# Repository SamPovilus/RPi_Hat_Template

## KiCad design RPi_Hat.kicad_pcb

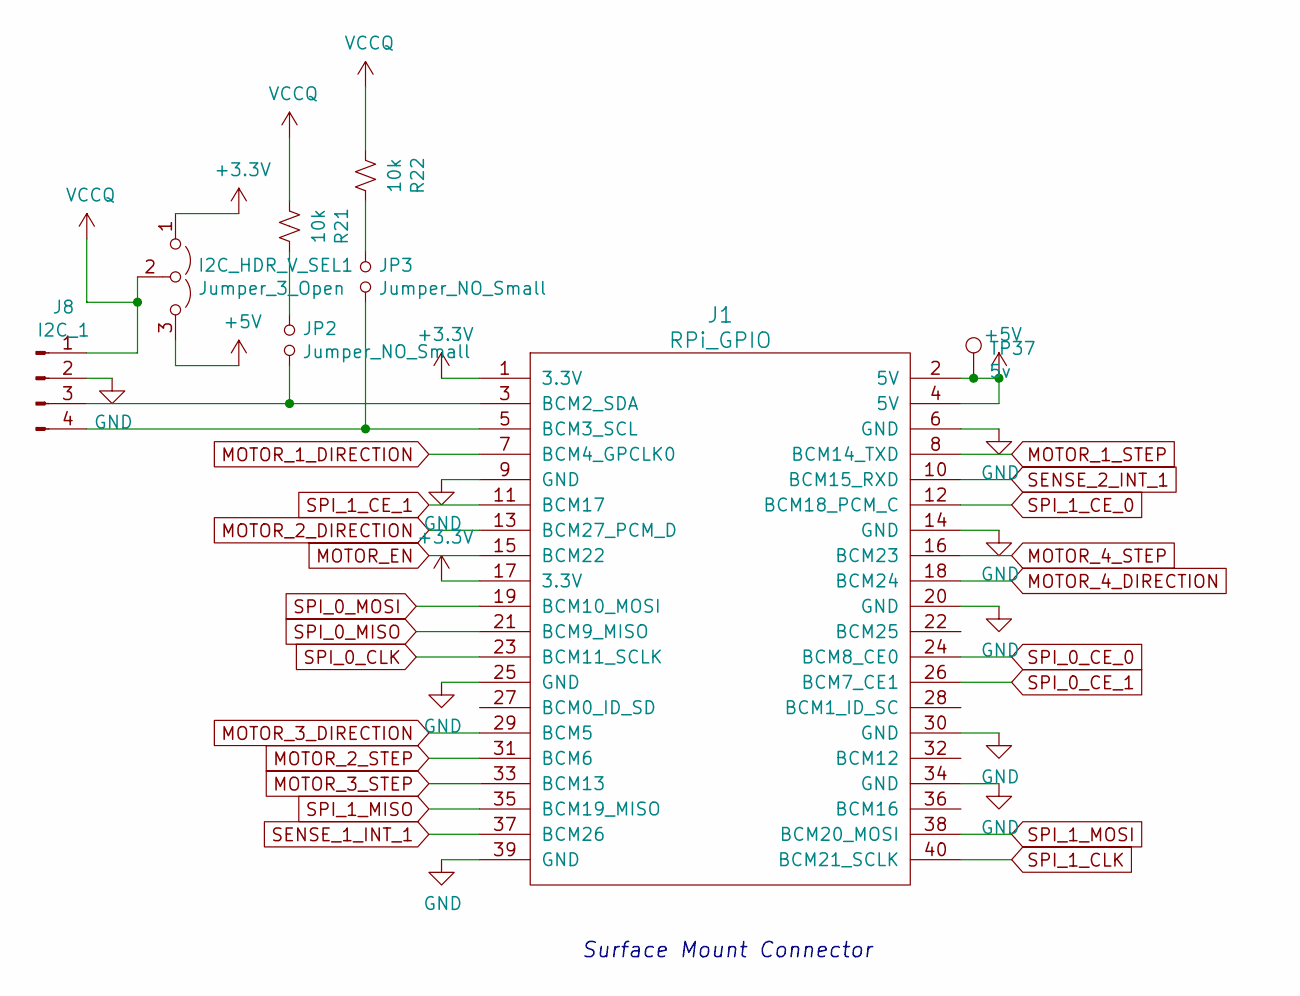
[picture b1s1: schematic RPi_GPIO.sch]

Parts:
I2C_HDR_V_SEL1: Jumper_3_Open; SAMTEC-TSM-103-01-X-SH
J1: RPi_GPIO; Samtec_HLE-120-02-XXX-DV-BE-XX-XX
J8: I2C_1; SAMTEC-TSM-102-01-X-DH
JP2, JP3: Jumper_NO_Small; SolderJumper-2_P1.3mm_Open_TrianglePad1.0x1.5mm
R21, R22: 10k; C_0805_2012Metric_Pad1.18x1.45mm_HandSolder
TP37: 5v; TestPoint_Keystone_5015_Micro-Minature

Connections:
+3V3: I2C_HDR_V_SEL1.1 (A), J1.1 (3.3V), J1.17 (3.3V); also elsewhere on the board
+5V: I2C_HDR_V_SEL1.3 (B), J1.2 (5V), J1.4 (5V), TP37.1; also elsewhere on the board
GND: J1.6 (GND), J1.9 (GND), J1.14 (GND), J1.20 (GND), J1.25 (GND), J1.30 (GND), J1.34 (GND), J1.39 (GND), J8.2; also elsewhere on the board
MOTOR_1_DIRECTION: J1.7 (BCM4_GPCLK0); also elsewhere on the board
MOTOR_1_STEP: J1.8 (BCM14_TXD); also elsewhere on the board
MOTOR_2_DIRECTION: J1.13 (BCM27_PCM_D); also elsewhere on the board
MOTOR_2_STEP: J1.31 (BCM6); also elsewhere on the board
MOTOR_3_DIRECTION: J1.29 (BCM5); also elsewhere on the board
MOTOR_3_STEP: J1.33 (BCM13); also elsewhere on the board
MOTOR_4_DIRECTION: J1.18 (BCM24); also elsewhere on the board
MOTOR_4_STEP: J1.16 (BCM23); also elsewhere on the board
MOTOR_EN: J1.15 (BCM22); also elsewhere on the board
unnamed 34: J1.3 (BCM2_SDA), J8.3, JP2.2; also elsewhere on the board
unnamed 35: J1.5 (BCM3_SCL), J8.4, JP3.2; also elsewhere on the board
unnamed 36: J1.22 (BCM25); also elsewhere on the board
unnamed 37: J1.27 (BCM0_ID_SD); also elsewhere on the board
unnamed 38: J1.28 (BCM1_ID_SC); also elsewhere on the board
unnamed 39: J1.32 (BCM12); also elsewhere on the board
unnamed 40: J1.36 (BCM16); also elsewhere on the board
unnamed: JP2.1, R21.1
unnamed: JP3.1, R22.1
SENSE_1_INT_1: J1.37 (BCM26); also elsewhere on the board
SENSE_2_INT_1: J1.10 (BCM15_RXD); also elsewhere on the board
SPI_0_CE_0: J1.24 (BCM8_CE0); also elsewhere on the board
SPI_0_CE_1: J1.26 (BCM7_CE1); also elsewhere on the board
SPI_0_CLK: J1.23 (BCM11_SCLK); also elsewhere on the board
SPI_0_MISO: J1.21 (BCM9_MISO); also elsewhere on the board
SPI_0_MOSI: J1.19 (BCM10_MOSI); also elsewhere on the board
SPI_1_CE_0: J1.12 (BCM18_PCM_C); also elsewhere on the board
SPI_1_CE_1: J1.11 (BCM17); also elsewhere on the board
SPI_1_CLK: J1.40 (BCM21_SCLK); also elsewhere on the board
SPI_1_MISO: J1.35 (BCM19_MISO); also elsewhere on the board
SPI_1_MOSI: J1.38 (BCM20_MOSI); also elsewhere on the board
VCCQ: I2C_HDR_V_SEL1.2 (C), J8.1, R21.2, R22.2

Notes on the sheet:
Surface Mount Connector

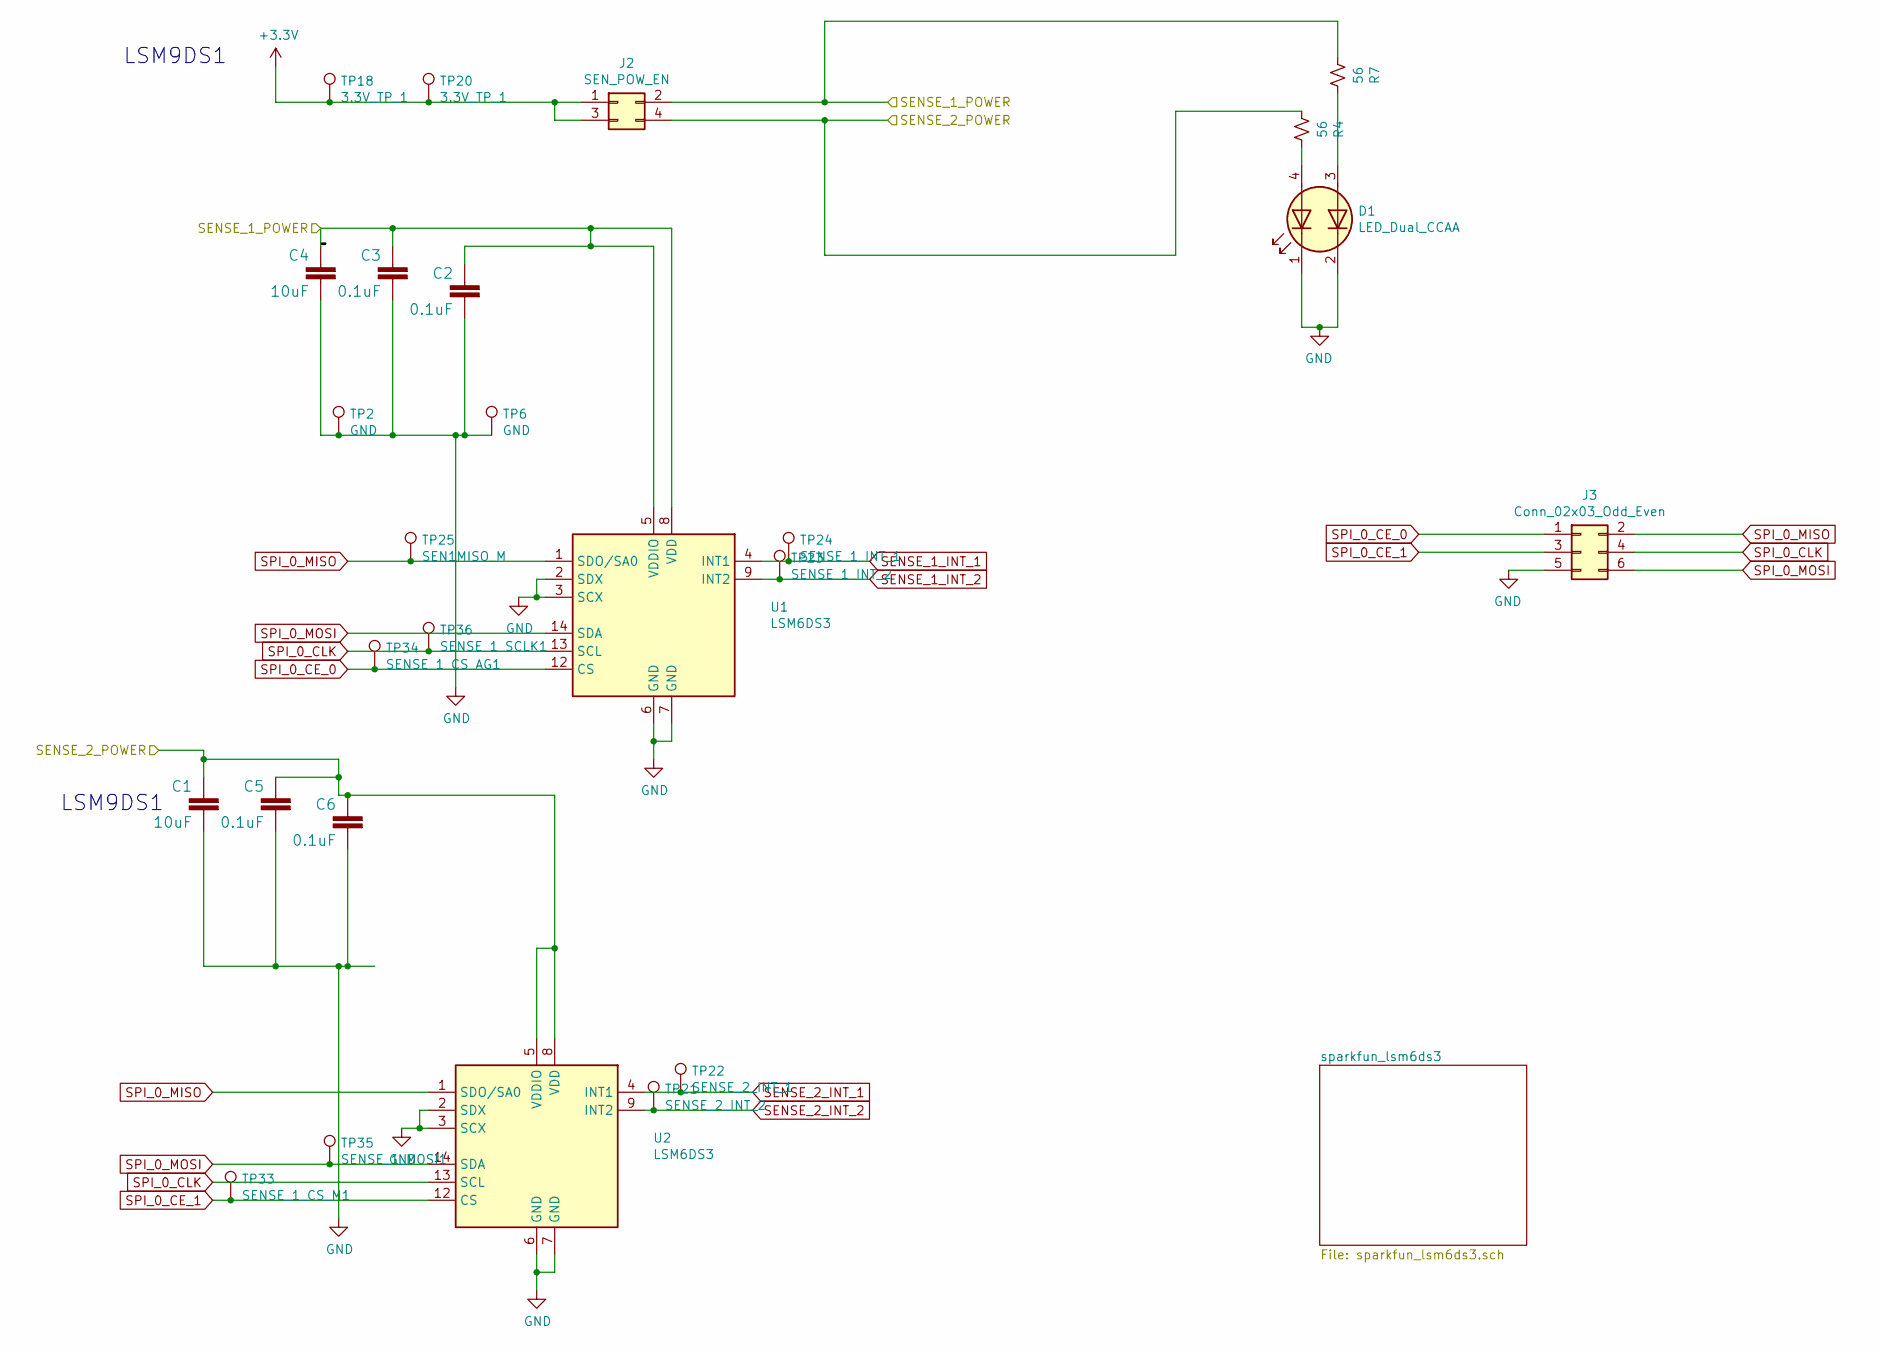
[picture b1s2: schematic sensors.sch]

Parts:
C1, C4: 10uF; C_0805_2012Metric_Pad1.18x1.45mm_HandSolder
C2, C3, C5, C6: 0.1uF; C_0805_2012Metric_Pad1.18x1.45mm_HandSolder
D1: LED_Dual_CCAA; LED_WURTH_ELECTRONIC_DUAL
J2: SEN_POW_EN; SAMTEC-TSM-102-01-X-DH
J3: Conn_02x03_Odd_Even; SAMTEC-TSM-103-01-X-DH
R4, R7: 56; C_0805_2012Metric_Pad1.18x1.45mm_HandSolder
TP2, TP6: GND; TestPoint_Keystone_5015_Micro-Minature
TP18, TP20: 3.3V_TP_1; TestPoint_Keystone_5015_Micro-Minature
TP21: SENSE_2_INT_2; TestPoint_Keystone_5015_Micro-Minature
TP22: SENSE_2_INT_1; TestPoint_Keystone_5015_Micro-Minature
TP23: SENSE_1_INT_2; TestPoint_Keystone_5015_Micro-Minature
TP24: SENSE_1_INT_1; TestPoint_Keystone_5015_Micro-Minature
TP25: SEN1MISO_M; TestPoint_Keystone_5015_Micro-Minature
TP33: SENSE_1_CS_M1; TestPoint_Keystone_5015_Micro-Minature
TP34: SENSE_1_CS_AG1; TestPoint_Keystone_5015_Micro-Minature
TP35: SENSE_1_MOSI1; TestPoint_Keystone_5015_Micro-Minature
TP36: SENSE_1_SCLK1; TestPoint_Keystone_5015_Micro-Minature
U1, U2: LSM6DS3; LGA-14_3x2.5mm_P0.5mm_LayoutBorder3x4y_for_6mil_board

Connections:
+3V3: J2.1, J2.3, TP18.1, TP20.1; also elsewhere on the board
/sensors/SENSE_1_POWER: C2.1, C3.1, C4.1, J2.2, R7.2, U1.5 (VDDIO), U1.8 (VDD)
/sensors/SENSE_2_POWER: C1.1, C5.1, C6.1, J2.4, R4.2, U2.5 (VDDIO), U2.8 (VDD)
GND: C1.2, C2.2, C3.2, C4.2, C5.2, C6.2, D1.1 (K1), D1.2 (K2), J3.5, TP2.1, TP6.1, U1.2 (SDX), U1.3 (SCX), U1.6 (GND), U1.7 (GND), U2.2 (SDX), U2.3 (SCX), U2.6 (GND), U2.7 (GND); also elsewhere on the board
unnamed: D1.3 (A2), R7.1
unnamed: D1.4 (A1), R4.1
SENSE_1_INT_1: TP24.1, U1.4 (INT1); also elsewhere on the board
SENSE_1_INT_2: TP23.1, U1.9 (INT2); also elsewhere on the board
SENSE_2_INT_1: TP22.1, U2.4 (INT1); also elsewhere on the board
SENSE_2_INT_2: TP21.1, U2.9 (INT2); also elsewhere on the board
SPI_0_CE_0: J3.1, TP34.1, U1.12 (CS); also elsewhere on the board
SPI_0_CE_1: J3.3, TP33.1, U2.12 (CS); also elsewhere on the board
SPI_0_CLK: J3.4, TP36.1, U1.13 (SCL), U2.13 (SCL); also elsewhere on the board
SPI_0_MISO: J3.2, TP25.1, U1.1 (SDO/SA0), U2.1 (SDO/SA0); also elsewhere on the board
SPI_0_MOSI: J3.6, TP35.1, U1.14 (SDA), U2.14 (SDA); also elsewhere on the board

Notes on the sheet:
LSM9DS1

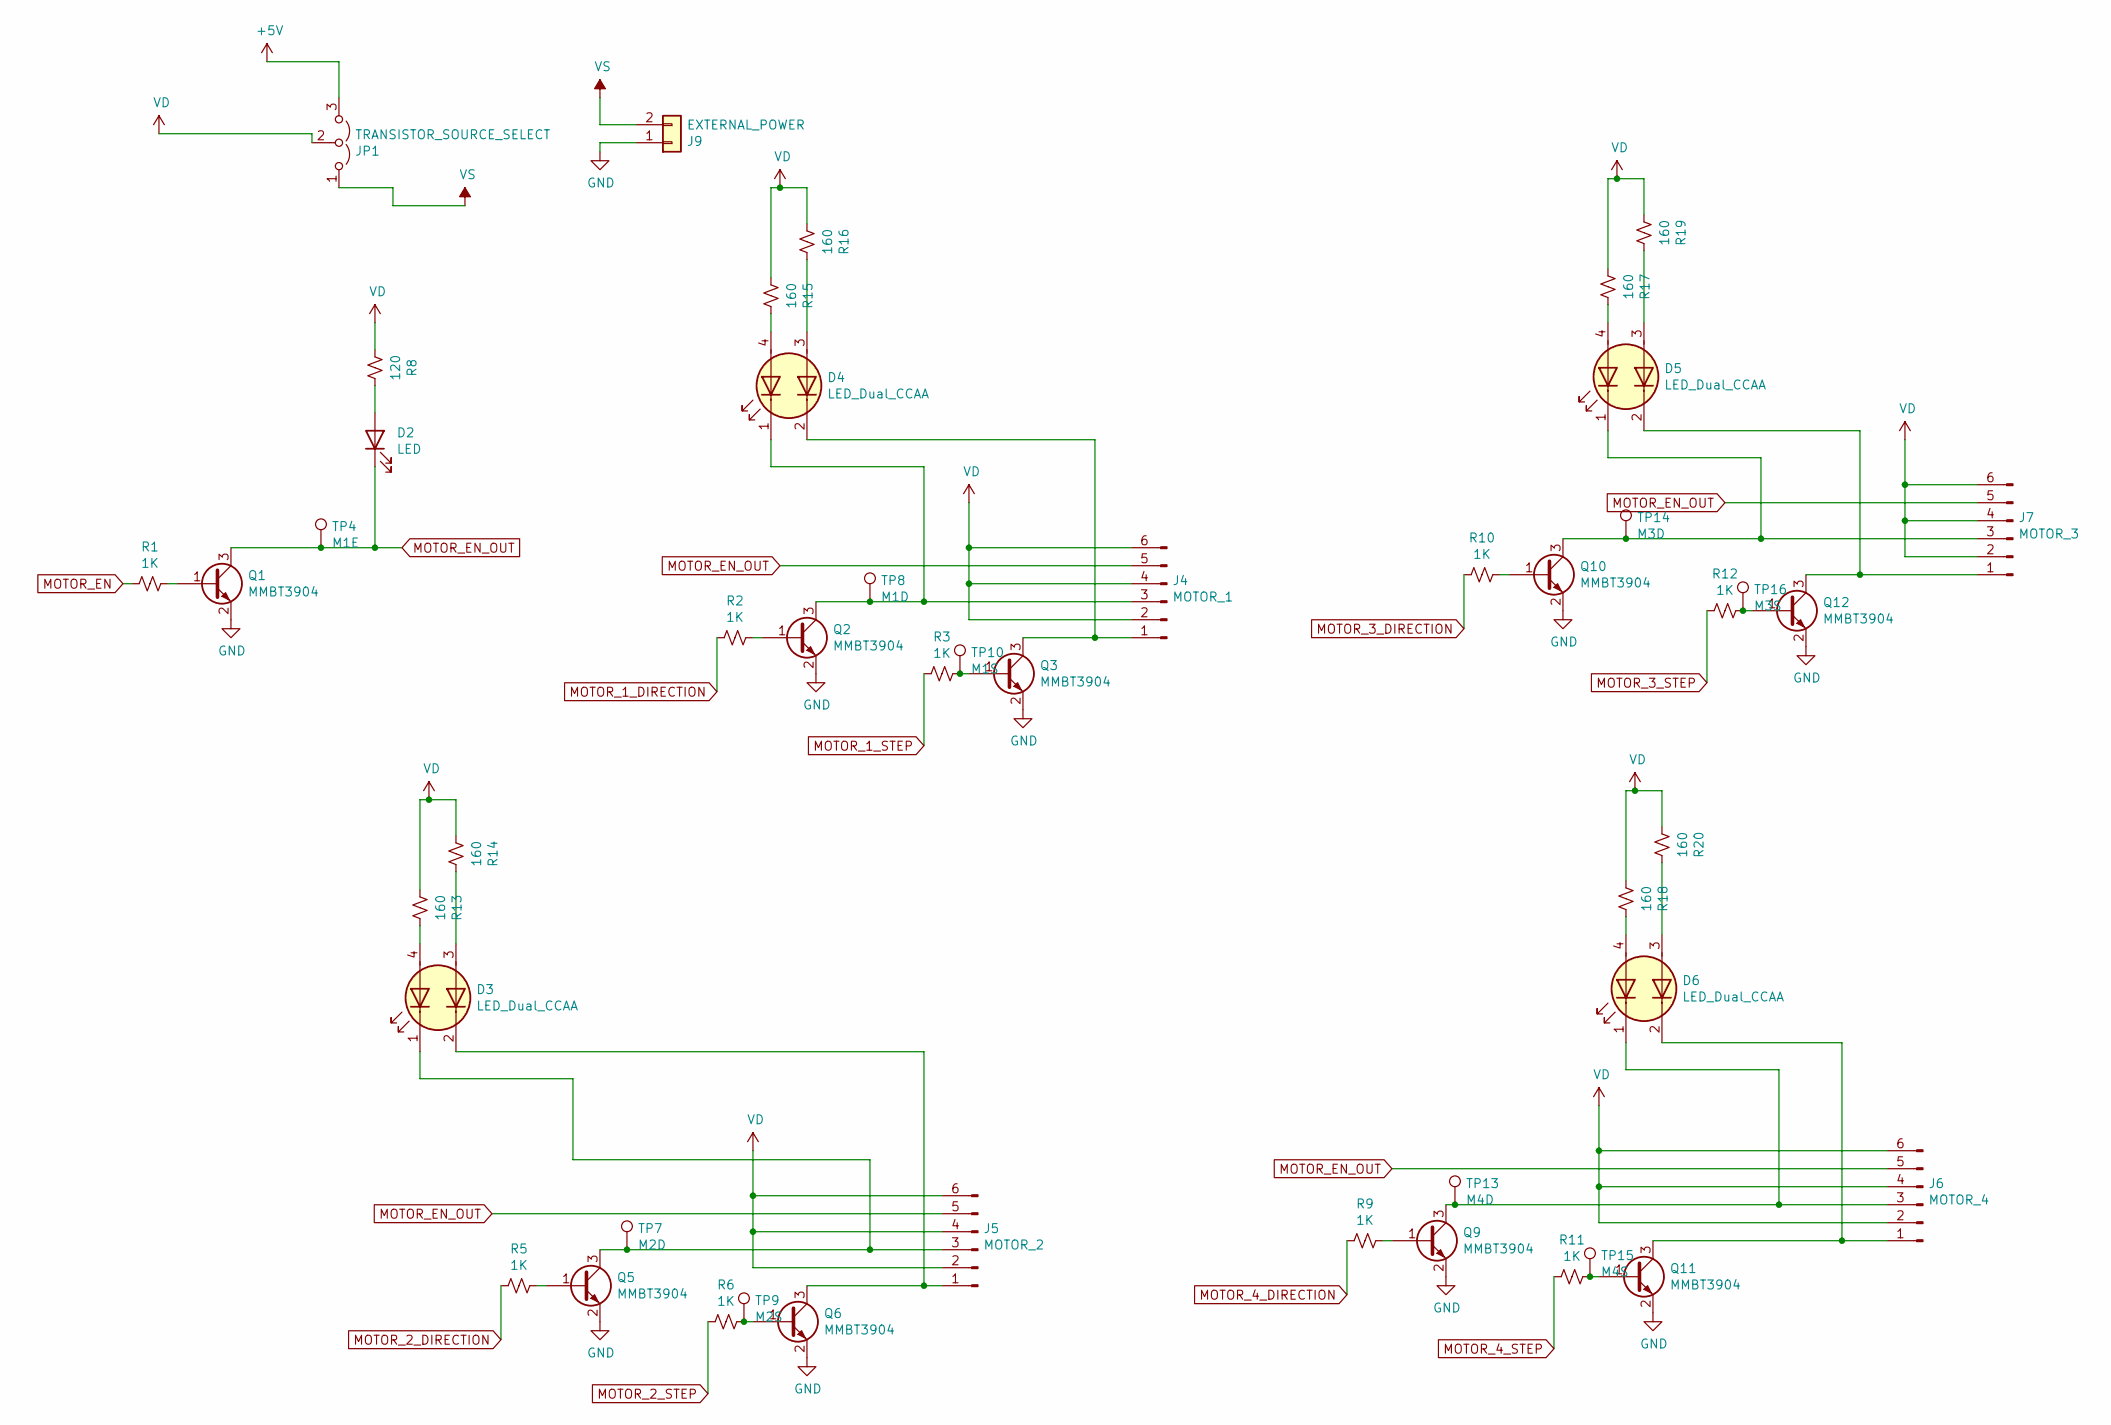
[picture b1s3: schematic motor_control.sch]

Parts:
D2: LED; LED_0805_2012Metric_Pad1.15x1.40mm_HandSolder
D3, D4, D5, D6: LED_Dual_CCAA; LED_WURTH_ELECTRONIC_DUAL
J4: MOTOR_1; SAMTEC-TSM-103-01-X-DH
J5: MOTOR_2; SAMTEC-TSM-103-01-X-DH
J6: MOTOR_4; SAMTEC-TSM-103-01-X-DH
J7: MOTOR_3; SAMTEC-TSM-103-01-X-DH
J9: EXTERNAL_POWER; SAMTEC-TSM-102-01-X-SH
JP1: TRANSISTOR_SOURCE_SELECT; SAMTEC-TSM-103-01-X-SH
Q1, Q2, Q3, Q5, Q6, Q9, Q10, Q11, Q12: MMBT3904; SOT-23
R1, R2, R3, R5, R6, R9, R10, R11, R12: 1K; C_0805_2012Metric_Pad1.18x1.45mm_HandSolder
R8: 120; C_0805_2012Metric_Pad1.18x1.45mm_HandSolder
R13, R14, R15, R16, R17, R18, R19, R20: 160; C_0805_2012Metric_Pad1.18x1.45mm_HandSolder
TP4: M1E; TestPoint_Keystone_5015_Micro-Minature
TP7: M2D; TestPoint_Keystone_5015_Micro-Minature
TP8: M1D; TestPoint_Keystone_5015_Micro-Minature
TP9: M2S; TestPoint_Keystone_5015_Micro-Minature
TP10: M1S; TestPoint_Keystone_5015_Micro-Minature
TP13: M4D; TestPoint_Keystone_5015_Micro-Minature
TP14: M3D; TestPoint_Keystone_5015_Micro-Minature
TP15: M4S; TestPoint_Keystone_5015_Micro-Minature
TP16: M3S; TestPoint_Keystone_5015_Micro-Minature

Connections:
+5V: JP1.3 (B); also elsewhere on the board
GND: J9.1, Q1.2 (E), Q2.2 (E), Q3.2 (E), Q5.2 (E), Q6.2 (E), Q9.2 (E), Q10.2 (E), Q11.2 (E), Q12.2 (E); also elsewhere on the board
MOTOR_1_DIRECTION: R2.2; also elsewhere on the board
MOTOR_1_STEP: R3.2; also elsewhere on the board
MOTOR_2_DIRECTION: R5.2; also elsewhere on the board
MOTOR_2_STEP: R6.2; also elsewhere on the board
MOTOR_3_DIRECTION: R10.2; also elsewhere on the board
MOTOR_3_STEP: R12.2; also elsewhere on the board
MOTOR_4_DIRECTION: R9.2; also elsewhere on the board
MOTOR_4_STEP: R11.2; also elsewhere on the board
MOTOR_EN: R1.2; also elsewhere on the board
MOTOR_EN_OUT: D2.1 (K), J4.5, J5.5, J6.5, J7.5, Q1.3 (C), TP4.1
unnamed: D2.2 (A), R8.1
unnamed: D3.1 (K1), J5.3, Q5.3 (C), TP7.1
unnamed: D3.2 (K2), J5.1, Q6.3 (C)
unnamed: D3.3 (A2), R14.1
unnamed: D3.4 (A1), R13.1
unnamed: D4.1 (K1), J4.3, Q2.3 (C), TP8.1
unnamed: D4.2 (K2), J4.1, Q3.3 (C)
unnamed: D4.3 (A2), R16.1
unnamed: D4.4 (A1), R15.1
unnamed: D5.1 (K1), J7.3, Q10.3 (C), TP14.1
unnamed: D5.2 (K2), J7.1, Q12.3 (C)
unnamed: D5.3 (A2), R19.1
unnamed: D5.4 (A1), R17.1
unnamed: D6.1 (K1), J6.3, Q9.3 (C), TP13.1
unnamed: D6.2 (K2), J6.1, Q11.3 (C)
unnamed: D6.3 (A2), R20.1
unnamed: D6.4 (A1), R18.1
unnamed: Q1.1 (B), R1.1
unnamed: Q2.1 (B), R2.1
unnamed: Q3.1 (B), R3.1, TP10.1
unnamed: Q5.1 (B), R5.1
unnamed: Q6.1 (B), R6.1, TP9.1
unnamed: Q9.1 (B), R9.1
unnamed: Q10.1 (B), R10.1
unnamed: Q11.1 (B), R11.1, TP15.1
unnamed: Q12.1 (B), R12.1, TP16.1
VD: J4.2, J4.4, J4.6, J5.2, J5.4, J5.6, J6.2, J6.4, J6.6, J7.2, J7.4, J7.6, JP1.2 (C), R8.2, R13.2, R14.2, R15.2, R16.2, R17.2, R18.2, R19.2, R20.2
VS: J9.2, JP1.1 (A)

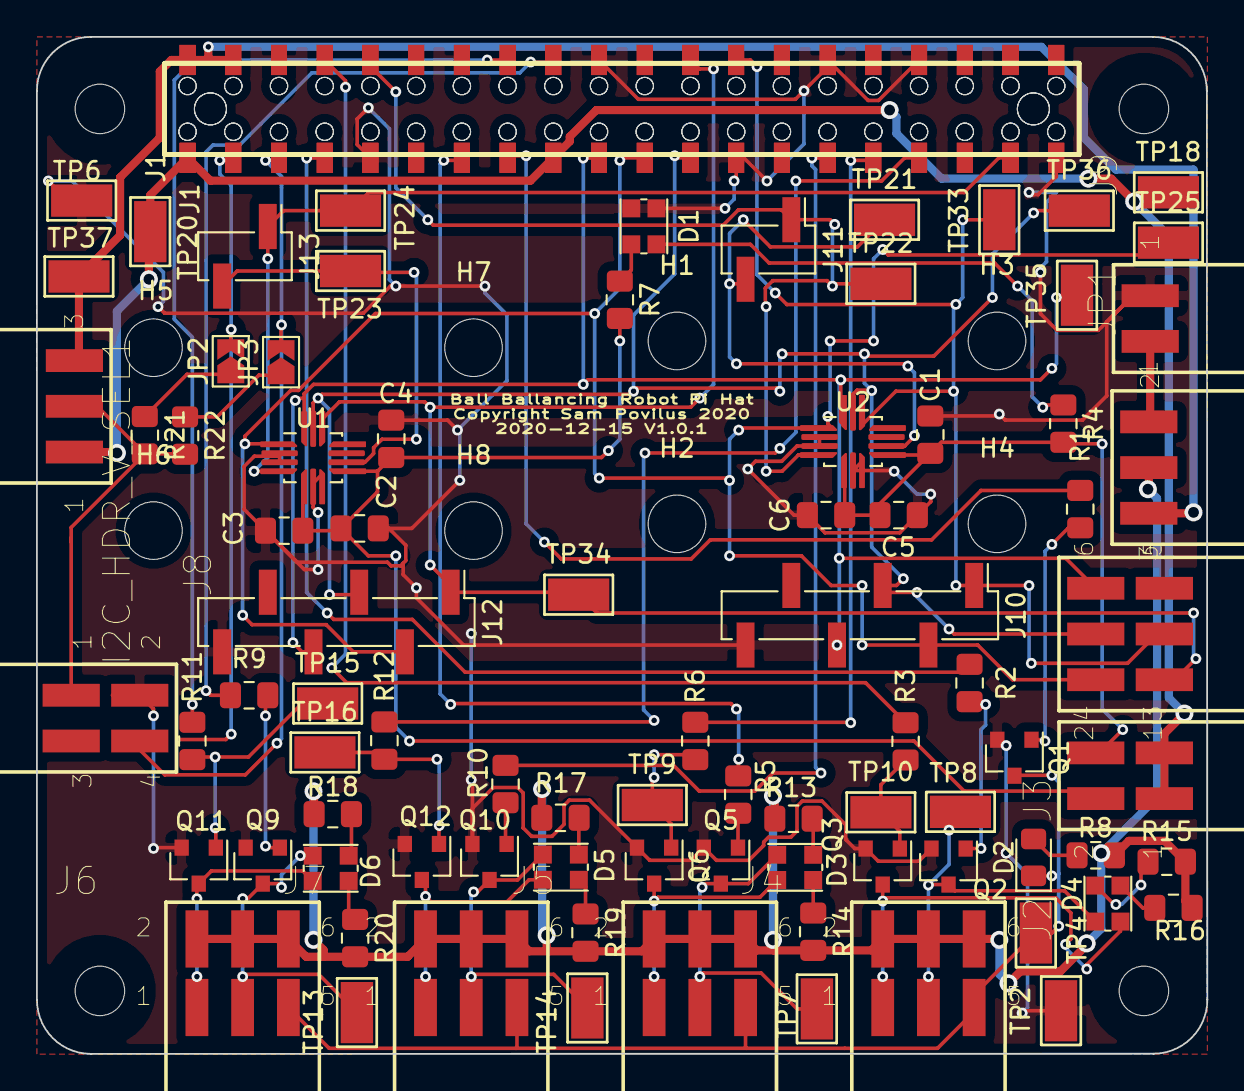
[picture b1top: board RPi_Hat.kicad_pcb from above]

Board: 2 copper layers, 65.0 x 56.5 mm, 94 parts (0 on the bottom side), 69 nets.

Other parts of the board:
H1, H2, H3, H4, H5, H6, H7, H8: MountingHole; MountingHole_3.2mm_M3
J1#2: RPi_GPIO; Samtec_HLE-120-02-XXX-DV-BE-XX-XX
J10, J12: Conn_01x06_Female; PinHeader_1x06_P2.54mm_Vertical_SMD_Pin1Left
J11, J13: Conn_01x02_Female; PinHeader_1x02_P2.54mm_Vertical_SMD_Pin1Left

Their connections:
+3V3: J1#2.1, J1#2.17; also elsewhere on the board
+5V: J1#2.2, J1#2.4; also elsewhere on the board
GND: J1#2.6, J1#2.9, J1#2.14, J1#2.20, J1#2.25, J1#2.30, J1#2.34, J1#2.39, J10.6, J12.6; also elsewhere on the board
MOTOR_1_DIRECTION: J1#2.7; also elsewhere on the board
MOTOR_1_STEP: J1#2.8; also elsewhere on the board
MOTOR_2_DIRECTION: J1#2.13; also elsewhere on the board
MOTOR_2_STEP: J1#2.31; also elsewhere on the board
MOTOR_3_DIRECTION: J1#2.29; also elsewhere on the board
MOTOR_3_STEP: J1#2.33; also elsewhere on the board
MOTOR_4_DIRECTION: J1#2.18; also elsewhere on the board
MOTOR_4_STEP: J1#2.16; also elsewhere on the board
MOTOR_EN: J1#2.15; also elsewhere on the board
unnamed 34: J1#2.3; also elsewhere on the board
unnamed 35: J1#2.5; also elsewhere on the board
unnamed 36: J1#2.22; also elsewhere on the board
unnamed 37: J1#2.27; also elsewhere on the board
unnamed 38: J1#2.28; also elsewhere on the board
unnamed 39: J1#2.32; also elsewhere on the board
unnamed 40: J1#2.36; also elsewhere on the board
SENSE_1_INT_1: J1#2.37, J13.1; also elsewhere on the board
SENSE_1_INT_2: J13.2; also elsewhere on the board
SENSE_2_INT_1: J1#2.10, J11.1; also elsewhere on the board
SENSE_2_INT_2: J11.2; also elsewhere on the board
SPI_0_CE_0: J1#2.24, J12.1; also elsewhere on the board
SPI_0_CE_1: J1#2.26, J10.1; also elsewhere on the board
SPI_0_CLK: J1#2.23, J10.3, J12.3; also elsewhere on the board
SPI_0_MISO: J1#2.21, J10.2, J12.2; also elsewhere on the board
SPI_0_MOSI: J1#2.19, J10.4, J12.4; also elsewhere on the board
SPI_1_CE_0: J1#2.12; also elsewhere on the board
SPI_1_CE_1: J1#2.11; also elsewhere on the board
SPI_1_CLK: J1#2.40; also elsewhere on the board
SPI_1_MISO: J1#2.35; also elsewhere on the board
SPI_1_MOSI: J1#2.38; also elsewhere on the board

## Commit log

2017-04-17 initial cut of adc development board
2017-04-17 adding mised files
2017-04-17 adding voltage references
2017-04-18 adding todo
2017-04-18 not sure
2017-04-19 movin to 0805 and 2mm headers (from 100 mil)
2017-04-22 pcb placed
2017-08-30 not really sure what i did
2020-11-15 added sensors and got working
2020-11-15 laid out ?
2020-11-15 motors * adding a header for external power for the drive transitiors and a jumper for slecting the source
2020-11-15 bom * regenerating bom after adding motor drive transitor voltage selector
2020-11-15 moving to lsm6d as lsm9d is not avalible and i don't use the magnomiter anyway
2020-11-16 orderd this version
2020-11-16 adding hacked apart footprint that works with 6mil trace and 6mil tracing
2020-11-16 crap, miso was disconnected from sensor 1, fixed it
2020-11-16 updating date on copyright silkscreen
2020-11-16 updating version on silk
2020-12-04 adding notes about how to fix for rev 1.x
2020-12-05 seperating sensor power, moving chip slect 0 test point to more approprate location
2020-12-06 added drive indicator led's, added power led for sensors
2020-12-06 extending lga pads to make soldering eaiser
2020-12-06 starting routing
2020-12-07 more todos
2020-12-10 more todo
2020-12-12 adding i2c pullups
2020-12-15 adding sparkfun module capability, modifying side connectors
2020-12-15 fixing one side connector
2020-12-15 remove test ponints for sensor power led's are good enough
2020-12-15 checked pin order on daughter card
2020-12-16 routed
2020-12-16 adding copyright notice
2020-12-24 not sure left this too long
2020-12-27 making SENSE_N_POWER a global lable
2021-01-11 adding notes on todo if I make another rev
2021-01-11 adding notes on todo if I make another rev, about transistor
2021-01-11 adding todo about qwiic
2021-02-24 README_ROBO.md * adding more ideas todo
2021-02-28 README_ROBOT.md * adding another todo idea

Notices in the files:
RPi_Hat.kicad_pcb:
Copyright Sam Povilus 2020
